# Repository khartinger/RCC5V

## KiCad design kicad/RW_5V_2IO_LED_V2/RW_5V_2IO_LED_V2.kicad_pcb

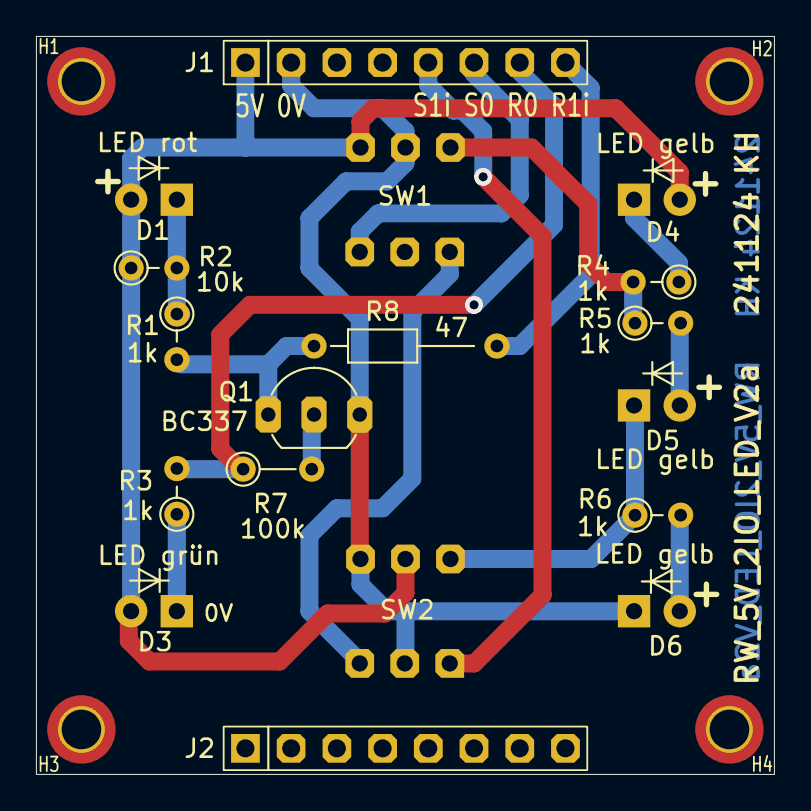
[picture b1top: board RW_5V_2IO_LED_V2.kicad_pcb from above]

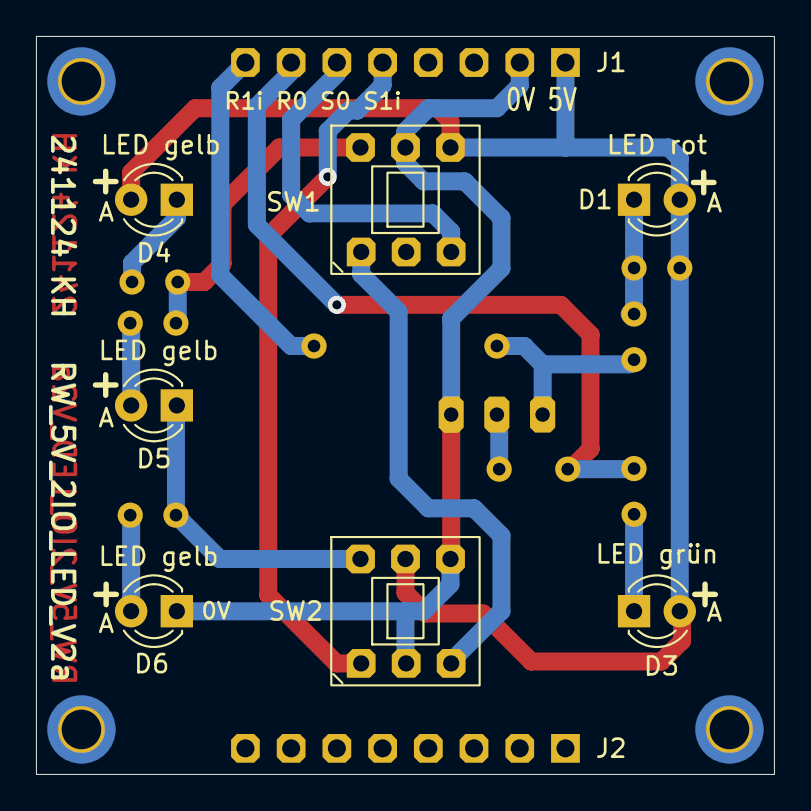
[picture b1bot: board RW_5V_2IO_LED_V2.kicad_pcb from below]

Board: 2 copper layers, 41.0 x 41.0 mm, 22 parts (7 on the bottom side), 16 nets.

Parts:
D1: LED rot; LED_D3.0mm
D3: LED grün; LED_D3.0mm
D4, D5, D6: LED gelb; LED_D3.0mm
H1, H2, H3, H4: MountingHole; MountingHole_2.2mm_M2_Pad_TopBottom_kh
J1, J2: Conn_01x08_Pin; PinSocket_1x08_P2.54mm_Vertical_11mm_kh
Q1: BC337; TO-92_Inline_Wide_custom
R1, R3, R4, R5, R6: 1k; R_Axial_DIN0204_L3.6mm_D1.6mm_P2.54mm_Vertical
R2: 10k; R_Axial_DIN0204_L3.6mm_D1.6mm_P2.54mm_Vertical_kh
R7: 100k; R_Axial_DIN0204_L3.6mm_D1.6mm_P3.81mm_Vertical_kh
R8: 47; R_Axial_DIN0204_L3.6mm_D1.6mm_P10,16mm_Horizontal
SW1, SW2: SW_Push_DPDT_8x8

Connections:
/0V: D6.1 (K), J1.2, Q1.3 (E), SW1.5 (B), SW2.2 (B), SW2.4 (A)
/LED_off: R4.2, R5.1, SW1.6 (C)
/LED_on: D5.1 (K), R6.1, SW2.6 (C)
/R0: J1.7, R3.2, R7.1
/R1i: J1.8, R8.2
/S0: J1.6, SW1.3 (C)
/S1i: J1.5, SW2.1 (A)
/S1ii: SW1.1 (A), SW2.3 (C)
/V_I2C: D1.2 (A), D3.2 (A), D4.2 (A), J1.1, R2.1, SW1.4 (A), SW2.5 (B)
unnamed: D1.1 (K), R1.1, R2.2
unnamed: D3.1 (K), R3.1
unnamed: D4.1 (K), R4.1
unnamed: D5.2 (A), R5.2
unnamed: D6.2 (A), R6.2
unnamed: Q1.2 (B), R7.2
unnamed: Q1.1 (C), R1.2, R8.1

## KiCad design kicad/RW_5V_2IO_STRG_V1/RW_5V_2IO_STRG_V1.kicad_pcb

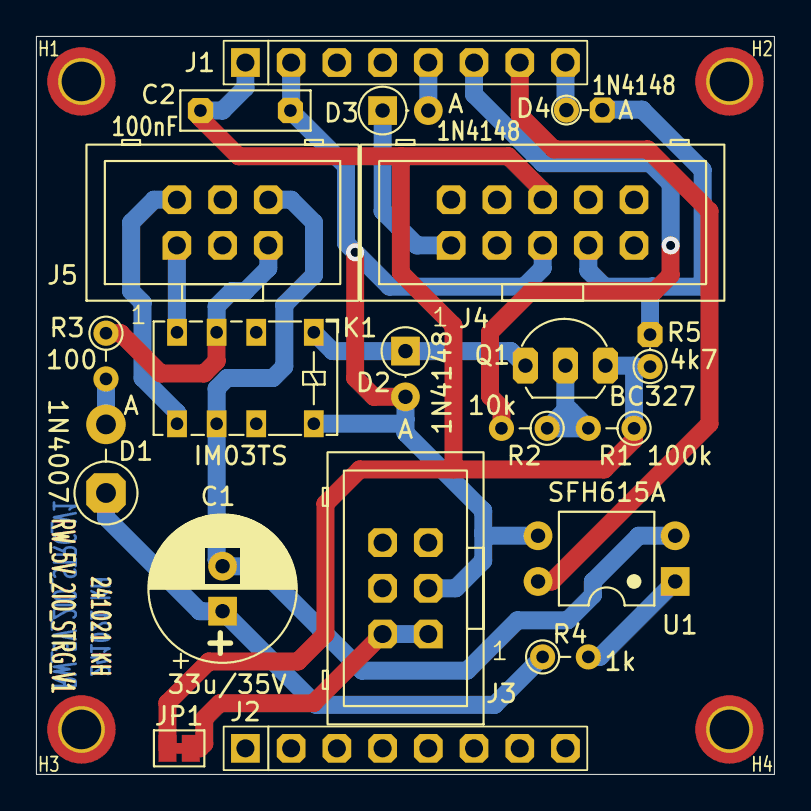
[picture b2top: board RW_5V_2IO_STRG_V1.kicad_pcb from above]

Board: 2 copper layers, 41.0 x 41.0 mm, 24 parts (0 on the bottom side), 18 nets.

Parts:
C1: 33u/35V; CP_Radial_D8.0mm_P2.50mm
C2: 100nF; C_Rect_L7.0mm_W2.0mm_P5.00mm_kh
D1: 1N4007; D_DO-41_SOD81_P3.81mm_Vertical_AnodeUp_kh
D2, D3: 1N4148; D_DO-35_SOD27_P2.54mm_Vertical_AnodeUp
D4: 1N4148; D_DO-35_P2.0mm_Vertical_AnodeUp_kh
H1, H2, H3, H4: MountingHole; MountingHole_2.2mm_M2_Pad_TopBottom_kh
J1, J2: Conn_01x08_Pin; PinSocket_1x08_P2.54mm_Vertical_kh
J3, J5: Box_02x03_P2.54_Vertical; Box_02x03_P2.54mm_Vertical_kh
J4: Box_02x05_P2.54_Vertical; Box_02x05_P2.54mm_Vertical_kh
JP1: Jumper_2_Bridged; SolderJumper-2_P1.3mm_Bridged_Pad1.0x1.5mm
K1: IM03TS; Relay_DPDT_AXICOM_IMSeries_Pitch5.08mm_rect_Pins
Q1: BC327; TO-92_Inline_Wide_2.2225
R1: 100k; R_Axial_DIN0204_L3.6mm_D1.6mm_P2.54mm_Vertical
R2: 10k; R_Axial_DIN0204_L3.6mm_D1.6mm_P2.54mm_Vertical
R3: 100; R_Axial_DIN0204_L3.6mm_D1.6mm_P2.54mm_Vertical
R4: 1k; R_Axial_DIN0204_L3.6mm_D1.6mm_P2.54mm_Vertical
R5: 4k7; R_Axial_P1.778mm_Vertical_kh
U1: SFH615A; DIP-4_W7.62mm

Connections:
/0V: C2.1, D2.2 (A), J1.2, J3.3, J4.5, K1.8, U1.3
/5V: J3.1, J3.2, JP1.2 (B)
/IN+: J5.1, K1.4
/IN-: J5.2, K1.5
/OUT+: J5.5, K1.3, R3.1
/OUT-: C1.2, J5.6, K1.6, U1.2
/Q1B: Q1.2 (B), R1.2, R2.1
/R0: J1.7, U1.4
/R1: D4.2 (A), J4.7, R5.2
/R1i: D4.1 (K), J1.8
/REL+: D2.1 (K), K1.1, Q1.1 (C)
/S0: J1.6, R2.2
/S1: D3.1 (K), J4.1
/S1i: D3.2 (A), J1.5
/V_I2C: C2.2, J1.1, J4.6, JP1.1 (A), Q1.3 (E), R1.1, R5.1
unnamed: D1.2 (A), R3.2
unnamed: C1.1, D1.1 (K), R4.1
unnamed: R4.2, U1.1

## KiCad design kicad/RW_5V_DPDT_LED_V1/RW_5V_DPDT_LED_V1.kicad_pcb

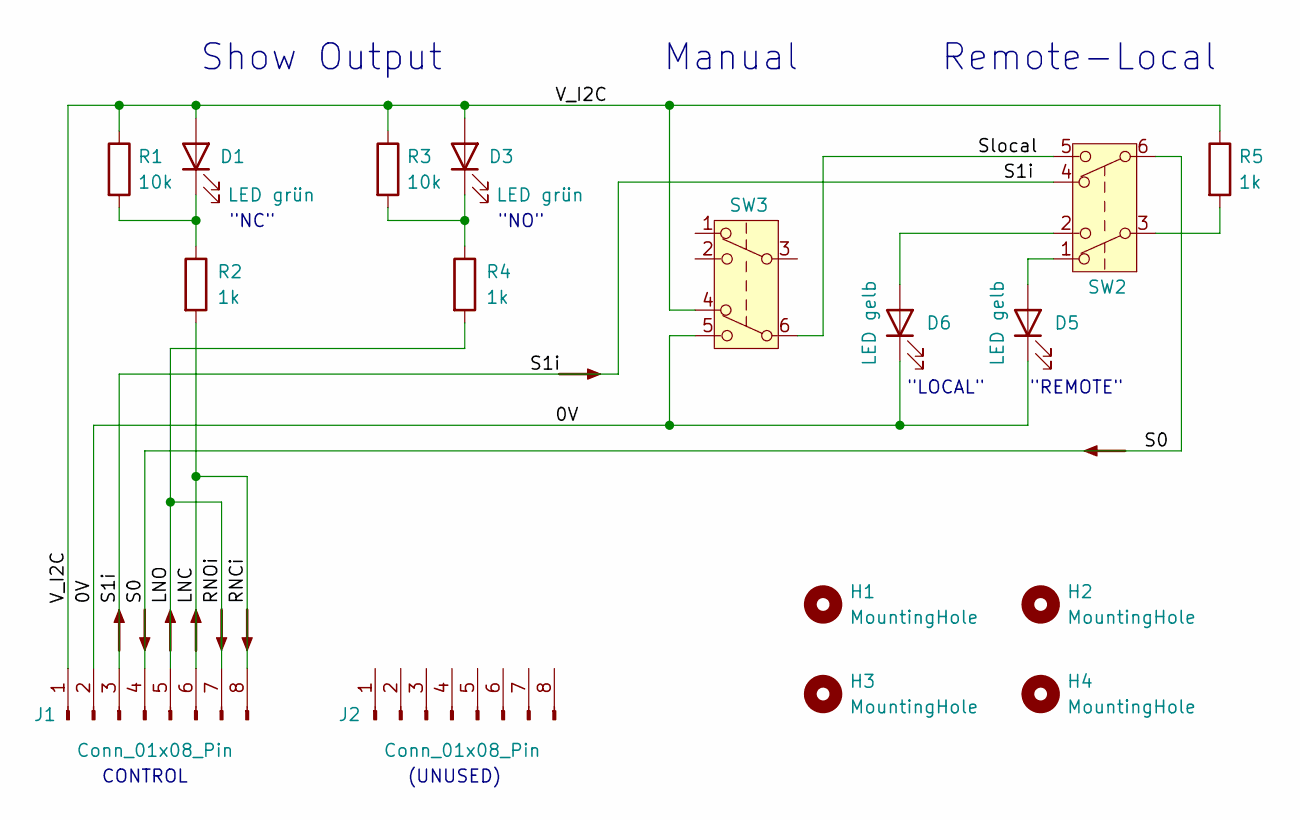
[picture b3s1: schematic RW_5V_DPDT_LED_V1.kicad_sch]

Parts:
D1, D3: LED grün; LED_D3.0mm
D5, D6: LED gelb; LED_D3.0mm
H1, H2, H3, H4: MountingHole; MountingHole_2.2mm_M2_Pad_TopBottom_kh
J1, J2: Conn_01x08_Pin; PinSocket_1x08_P2.54mm_Vertical_11mm_kh
R1, R3: 10k; R_Axial_DIN0204_L3.6mm_D1.6mm_P2.54mm_Vertical
R2, R4: 1k; R_Axial_DIN0207_L6.3mm_D2.5mm_P15.24mm_Horizontal_kh
R5: 1k; R_Axial_DIN0204_L3.6mm_D1.6mm_P2.54mm_Vertical
SW2, SW3: SW_Push_DPDT_8x8

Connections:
/0V: D5.1 (K), D6.1 (K), J1.2, SW3.5 (B)
/LNC: J1.6, J1.8, R2.2
/LNO: J1.5, J1.7, R4.2
/S0: J1.4, SW2.6 (C)
/S1i: J1.3, SW2.4 (A)
/Slocal: SW2.5 (B), SW3.6 (C)
/V_I2C: D1.2 (A), D3.2 (A), J1.1, R1.1, R3.1, R5.1, SW3.4 (A)
unnamed: D1.1 (K), R1.2, R2.1
unnamed: D3.1 (K), R3.2, R4.1
unnamed: D5.2 (A), SW2.1 (A)
unnamed: D6.2 (A), SW2.2 (B)
unnamed: R5.2, SW2.3 (C)

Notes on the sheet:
(UNUSED)
"LOCAL"
Manual
"REMOTE"
Remote-Local
CONTROL
Show Output
"NC"
"NO"

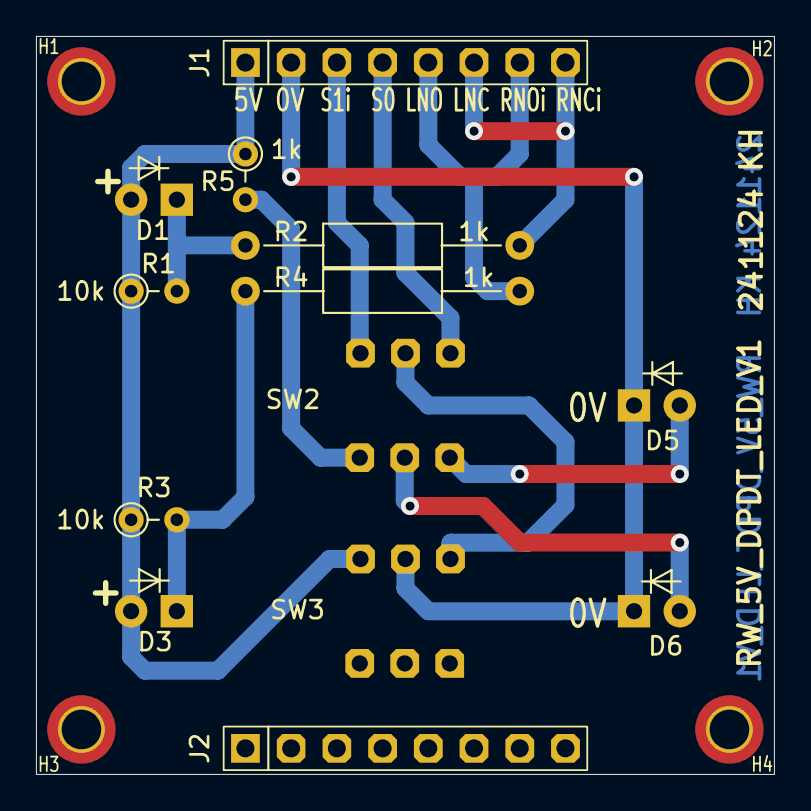
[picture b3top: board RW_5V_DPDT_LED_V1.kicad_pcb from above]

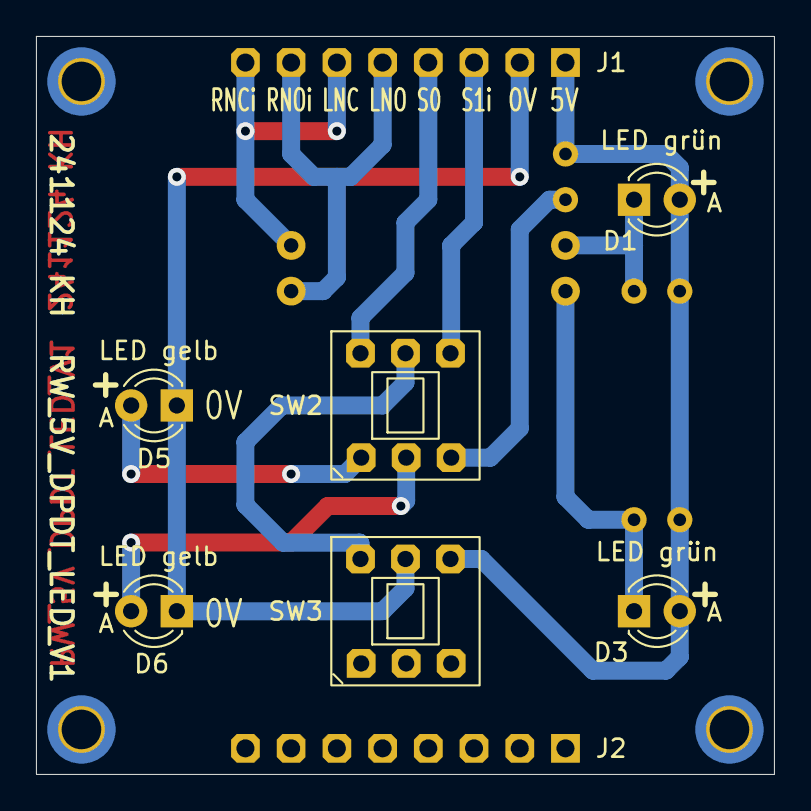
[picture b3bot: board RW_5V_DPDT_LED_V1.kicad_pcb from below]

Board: 2 copper layers, 41.0 x 41.0 mm, 17 parts (6 on the bottom side), 12 nets.

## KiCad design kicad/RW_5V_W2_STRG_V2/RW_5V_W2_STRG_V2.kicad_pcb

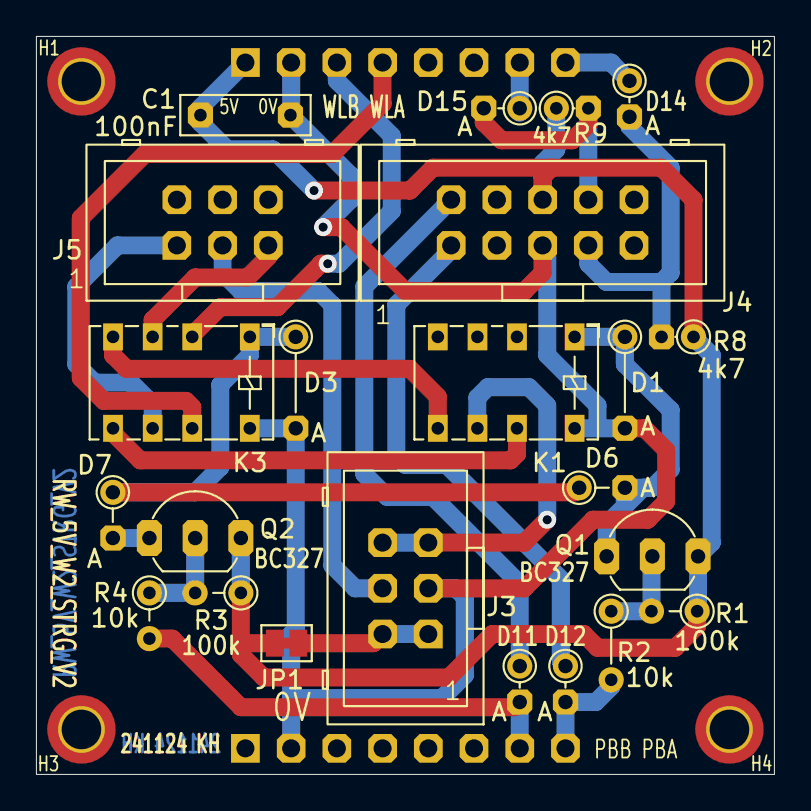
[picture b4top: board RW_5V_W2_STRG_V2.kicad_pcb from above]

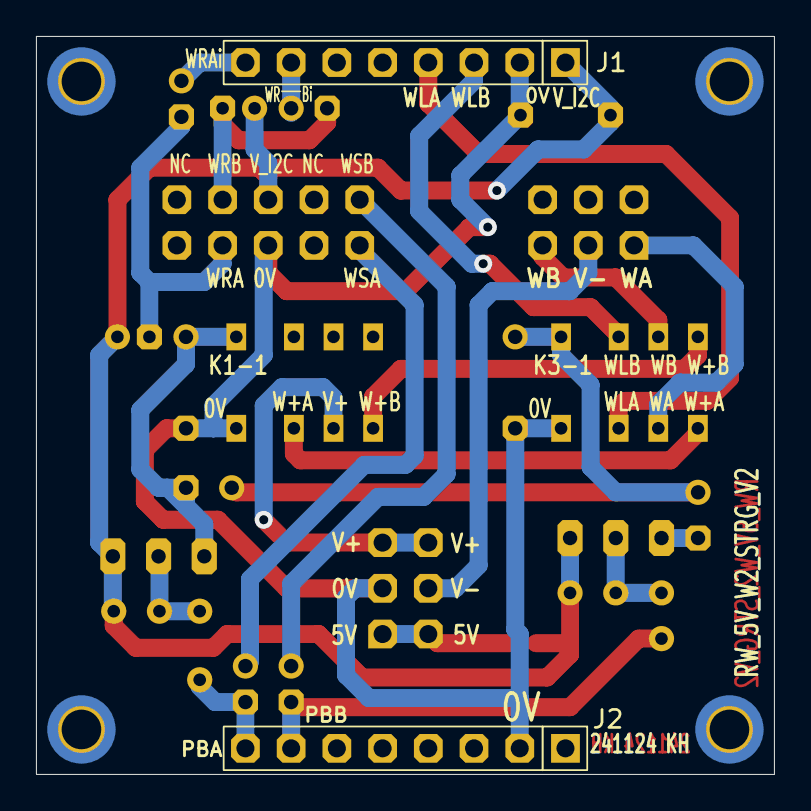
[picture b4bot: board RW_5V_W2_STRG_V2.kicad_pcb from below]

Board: 2 copper layers, 41.0 x 41.0 mm, 29 parts (2 on the bottom side), 24 nets.

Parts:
C1: 100nF; C_Rect_L7.0mm_W2.0mm_P5.00mm_kh
D1, D3: 1N4148; D_DO-35_SOD27_P5.08mm_Vertical_AnodeUp_kh
D6, D7: 1N4148; D_DO-35_SOD27_P2.54mm_Vertical_AnodeUp_kh
D11, D12, D14, D15: 1N4148; D_DO-35_P2.0mm_Vertical_AnodeUp_kh
H1, H2, H3, H4: MountingHole; MountingHole_2.2mm_M2_Pad_TopBottom_kh
J1, J2: Conn_01x08_Pin; PinHeader_1x08_P2.54mm_Vertical_kh
J3, J5: Box_02x03_P2.54_Vertical; Box_02x03_P2.54mm_Vertical_kh
J4: Box_02x05_P2.54_Vertical; Box_02x05_P2.54mm_Vertical_kh
JP1: Jumper_2_Bridged; SolderJumper-2_P1.3mm_Bridged_Pad1.0x1.5mm
K1, K3: IM03TS; Relay_DPDT_AXICOM_IMSeries_Pitch5.08mm_rect_Pins
Q1, Q2: BC327; TO-92_Inline_Wide_custom
R1, R3: 100k; R_Axial_DIN0204_L3.6mm_D1.6mm_P2.54mm_Vertical
R2: 10k; R_Axial_DIN0204_L3.6mm_D1.6mm_P3.81mm_Vertical_kh
R4: 10k; R_Axial_DIN0204_L3.6mm_D1.6mm_P2.54mm_Vertical
R8, R9: 4k7; R_Axial_P1.778mm_Vertical_kh

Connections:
/0V: C1.1, D1.2 (A), D3.2 (A), J1.2, J2.2, J3.3, J4.5, K1.8, K3.8
/5V: J3.1, J3.2, JP1.1 (A)
/K_dir: D1.1 (K), D6.2 (A), K1.1, Q1.1 (C)
/K_on: D3.1 (K), D6.1 (K), D7.1 (K), K3.1
/PBA: D12.2 (A), J2.8, R2.2
/PBB: D11.2 (A), J2.7, R4.2
/V+: J3.5, J3.6, K1.6
/V-: J3.4, J5.3
/V_I2C: C1.2, J1.1, J4.6, JP1.2 (B), Q1.3 (E), Q2.3 (E), R1.1, R3.1, R8.1, R9.1
/W+A: K1.7, K3.5
/W+B: K1.5, K3.4
/WA: J5.1, K3.6
/WB: J5.5, K3.3
/WLA: J1.4, K3.7
/WLB: J1.3, K3.2
/WRA: D14.2 (A), J4.7, R8.2
/WRAi: D14.1 (K), J1.8
/WRB: D15.2 (A), J4.8, R9.2
/WRBi: D15.1 (K), J1.7
/WSA: D12.1 (K), J4.1
/WSB: D11.1 (K), J4.2
unnamed: D7.2 (A), Q2.1 (C)
unnamed: Q1.2 (B), R1.2, R2.1
unnamed: Q2.2 (B), R3.2, R4.1

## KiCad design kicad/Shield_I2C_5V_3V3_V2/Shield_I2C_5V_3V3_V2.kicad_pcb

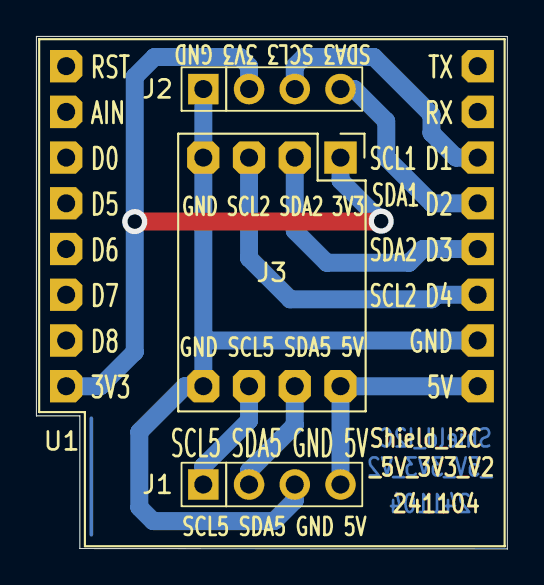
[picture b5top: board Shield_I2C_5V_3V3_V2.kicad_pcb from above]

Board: 2 copper layers, 26.2 x 28.5 mm, 4 parts (0 on the bottom side), 9 nets.

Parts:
J1: Conn_01x04_Pin; PinSocket_1x04_P2.54mm_Vertical_kh
J2: Conn_01x04_Socket; PinSocket_1x04_P2.54mm_Vertical_kh
J3: Converter_2x_3V3_5V
U1: WeMos_D1_mini; WEMOS_D1_mini_kh_shield_2

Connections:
/3V3: J2.2, J3.1, U1.8 (3V3)
/5V: J1.4, J3.8, U1.9 (5V)
/GND: J1.3, J2.1, J3.4 (PIN_4), J3.5, U1.10 (GND)
/SCL2: J3.3, U1.11 (D4)
/SCL3: J2.3, U1.14 (SCL/D1)
/SCL5: J1.1, J3.6
/SDA2: J3.2 (3A), U1.12 (D3)
/SDA3: J2.4, U1.13 (SDA/D2)
/SDA5: J1.2, J3.7
